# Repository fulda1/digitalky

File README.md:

# digitálky
jednoduché modulární hodiny

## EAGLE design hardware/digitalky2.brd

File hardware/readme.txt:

Hardware components
- schematic
- board
- gerber file

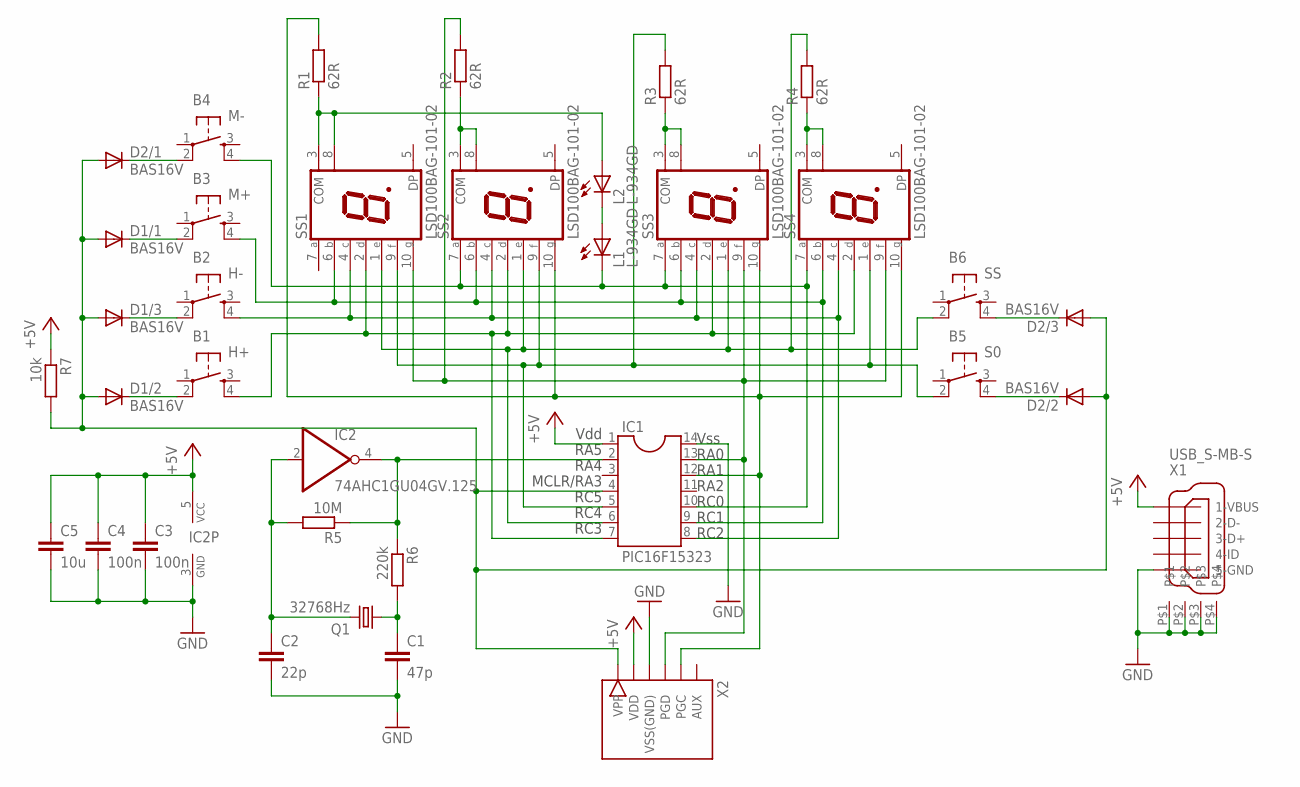
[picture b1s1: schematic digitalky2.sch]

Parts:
B1: H+; TD-03
B2: H-; TD-03
B3: M+; TD-03
B4: M-; TD-03
B5: S0; TD-03
B6: SS; TD-03
C1: 47p; C0805
C2: 22p; C0805
C3, C4: 100n; C0805
C5: 10u; C1206
D1, D2: BAS16V; SOT363
IC1: PIC16F15323; SO-14
IC2: 74AHC1GU04GV.125; SOT23-5
L1, L2: L-934GD; LED3MM
Q1: 32768Hz; TC38H
R1, R2, R3, R4: 62R; R0805
R5: 10M; R0805
R6: 220k; R0805
R7: 10k; R0805
SS1, SS2, SS3, SS4: LSD100BAG-101-02; SA10-21-R
X1: USB_S-MB-S; USB-MB-S
X2: PICKITXS; 6PIN3

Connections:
+5V: C3.1, C4.1, C5.1, IC1.1, IC2.5 (VCC), R7.1, X1.VBUS (1-VBUS), X2.P$2 (VDD)
GND: C1.2, C2.2, C3.2, C4.2, C5.2, IC1.14, IC2.3 (GND), X1.GND (5-GND), X1.P$1, X1.P$2, X1.P$3, X1.P$4, X2.P$3 (VSS(GND))
unnamed: B4.4, IC1.10, L1.K (C), SS2.7 (A), SS3.7 (A), SS4.7 (A)
unnamed: B3.4, IC1.9, SS1.6 (B), SS2.6 (B), SS3.6 (B), SS4.6 (B)
unnamed: B2.4, IC1.8, SS1.4 (C), SS2.4 (C), SS3.4 (C), SS4.4 (C)
unnamed: B1.4, IC1.7, SS1.2 (D), SS2.2 (D), SS3.2 (D), SS4.2 (D)
unnamed: B6.2, IC1.6, R4.2, SS1.1 (E), SS2.1 (E), SS3.1 (E)
unnamed: B6.4, D2.4 (C)
unnamed: L2.A, R1.1, SS1.3 (COM), SS1.8 (COM)
unnamed: B5.2, IC1.5, R3.2, SS1.9 (F), SS2.9 (F), SS4.1 (E)
unnamed: L1.A, L2.K (C)
unnamed: IC1.12, R1.2, SS2.10 (G), SS3.10 (G), SS4.10 (G), X2.P$5 (PGC)
unnamed: R2.1, SS2.3 (COM), SS2.8 (COM)
unnamed: IC1.2, IC2.4 (O), R5.1, R6.1
unnamed: C2.1, IC2.2 (I), Q1.2, R5.2
unnamed: R3.1, SS3.3 (COM), SS3.8 (COM)
unnamed: C1.1, Q1.1, R6.2
unnamed: R4.1, SS4.3 (COM), SS4.8 (COM)
unnamed: D1.1 (A), D1.2 (A), D1.3 (A), D2.1 (A), D2.2 (A), D2.3 (A), IC1.4, R7.2, X2.P$1 (VPP)
unnamed: B4.2, D2.6 (C)
unnamed: B3.2, D1.6 (C)
unnamed: B2.2, D1.4 (C)
unnamed: B1.2, D1.5 (C)
unnamed: B5.4, D2.5 (C)
unnamed: IC1.13, R2.2, SS1.10 (G), SS3.9 (F), SS4.9 (F), X2.P$4 (PGD)

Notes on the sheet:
RA0
Vss
RA1
RA2
MCLR/RA3
RA4
RA5
Vdd
RC0
RC1
RC2
RC3
RC4
RC5

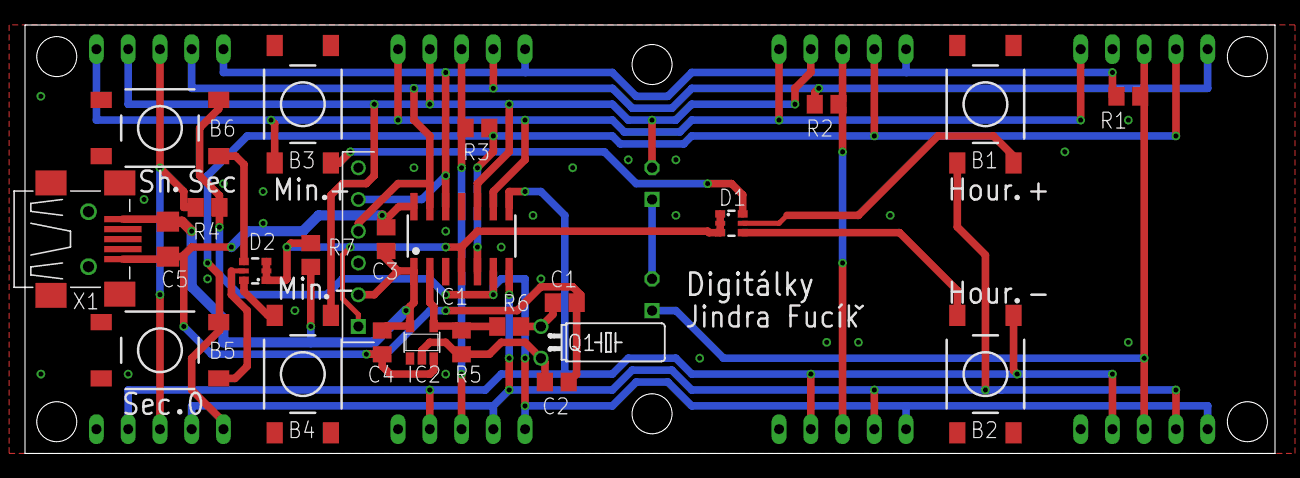
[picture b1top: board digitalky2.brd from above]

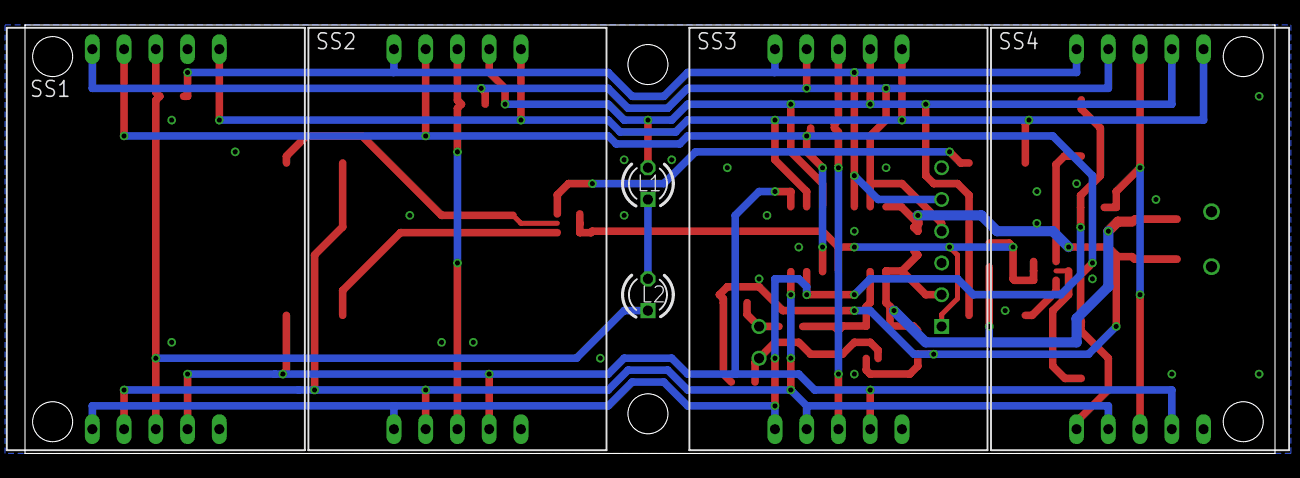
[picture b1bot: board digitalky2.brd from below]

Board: 2 copper layers, 100.0 x 34.3 mm, 31 parts (6 on the bottom side), 25 nets.

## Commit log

2022-04-05 Create LICENSE
